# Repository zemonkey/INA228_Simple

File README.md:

# INA228_Simple
 A Current Sensing Module with Input protection for INA228

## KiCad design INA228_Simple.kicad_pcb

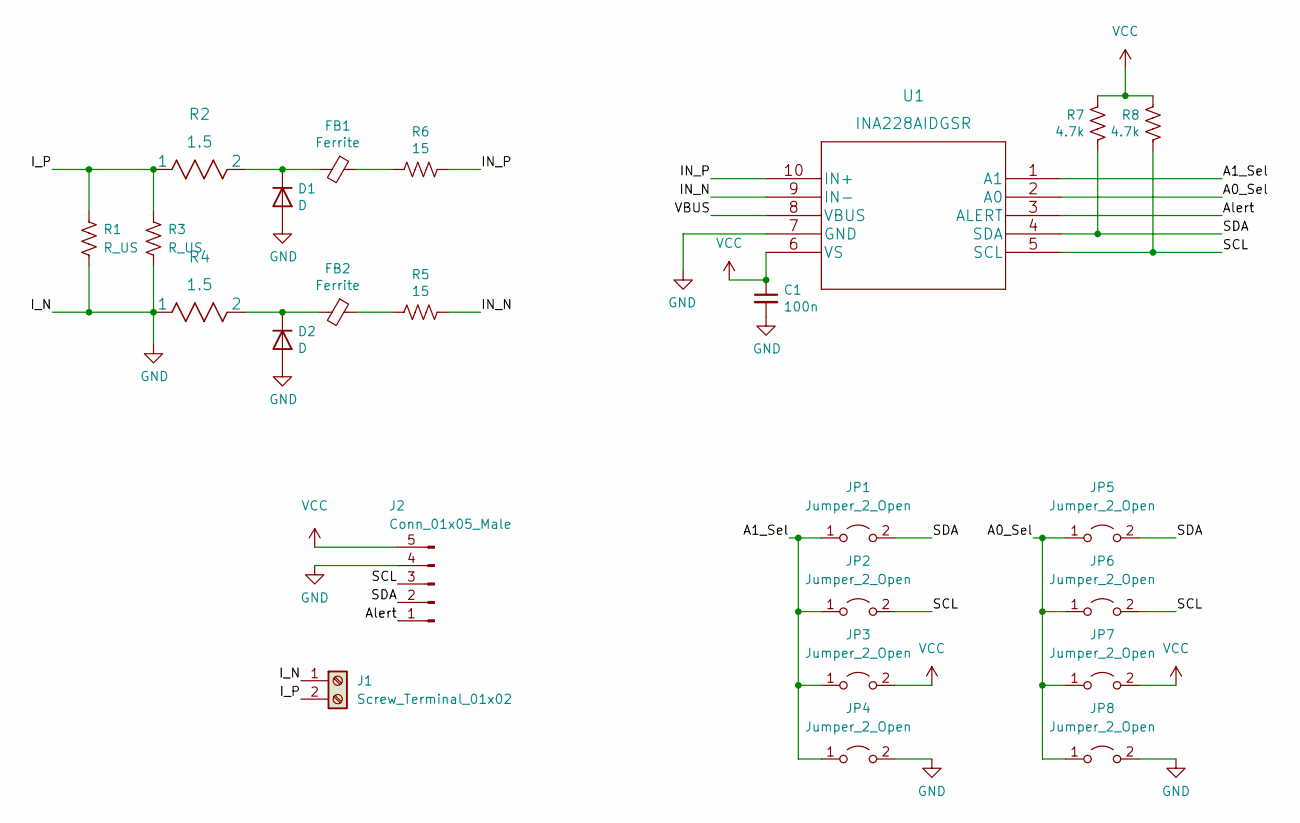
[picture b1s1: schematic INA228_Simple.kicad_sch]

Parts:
C1: 100n; C_0603_1608Metric_Pad1.08x0.95mm_HandSolder
D1, D2: D; D_SMA_Handsoldering
FB1, FB2: Ferrite; L_0603_1608Metric_Pad1.05x0.95mm_HandSolder
J1: Screw_Terminal_01x02; TerminalBlock_RND_205-00067_1x02_P7.50mm_Horizontal
J2: Conn_01x05_Male; PinSocket_1x05_P2.54mm_Vertical
JP1, JP2, JP3, JP4, JP5, JP6, JP7, JP8: Jumper_2_Open; TestPoint_2Pads_Pitch2.54mm_Drill0.8mm
R1: R_US; R_Axial_DIN0414_L11.9mm_D4.5mm_P15.24mm_Horizontal
R2, R4: 1.5; FKN50SJR-52-1R5
R3: R_US; R_2512_6332Metric_Pad1.40x3.35mm_HandSolder
R5, R6: 15; R_0603_1608Metric_Pad0.98x0.95mm_HandSolder
R7, R8: 4.7k; R_0603_1608Metric_Pad0.98x0.95mm_HandSolder
U1: INA228AIDGSR; VSSOP-10_3x3mm_P0.5mm

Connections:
/A0_Sel: JP5.1 (A), JP6.1 (A), JP7.1 (A), JP8.1 (A), U1.2 (A0)
/A1_Sel: JP1.1 (A), JP2.1 (A), JP3.1 (A), JP4.1 (A), U1.1 (A1)
/Alert: J2.1, U1.3 (ALERT)
/IN_N: R5.1, U1.9 (IN-)
/IN_P: R6.1, U1.10 (IN+)
/I_P: J1.2, R1.1, R2.1, R3.1
/SCL: J2.3, JP2.2 (B), JP6.2 (B), R8.2, U1.5 (SCL)
/SDA: J2.2, JP1.2 (B), JP5.2 (B), R7.2, U1.4 (SDA)
/VBUS: U1.8 (VBUS)
GND: C1.2, D1.2 (A), D2.2 (A), J1.1, J2.4, JP4.2 (B), JP8.2 (B), R1.2, R3.2, R4.1, U1.7 (GND)
unnamed: D1.1 (K), FB1.2, R2.2
unnamed: D2.1 (K), FB2.2, R4.2
unnamed: FB1.1, R6.2
unnamed: FB2.1, R5.2
VCC: C1.1, J2.5, JP3.2 (B), JP7.2 (B), R7.1, R8.1, U1.6 (VS)

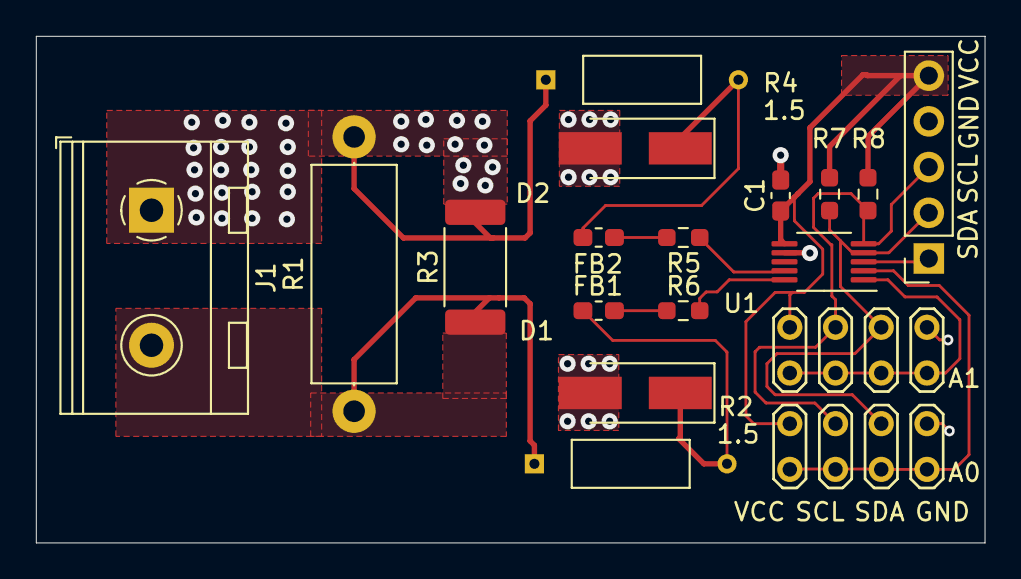
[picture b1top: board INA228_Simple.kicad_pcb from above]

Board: 2 copper layers, 52.7 x 28.1 mm, 24 parts (0 on the bottom side), 14 nets.

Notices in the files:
parts and their libraries:
Copyright 2021 Accelerated Designs. All rights reserved.
